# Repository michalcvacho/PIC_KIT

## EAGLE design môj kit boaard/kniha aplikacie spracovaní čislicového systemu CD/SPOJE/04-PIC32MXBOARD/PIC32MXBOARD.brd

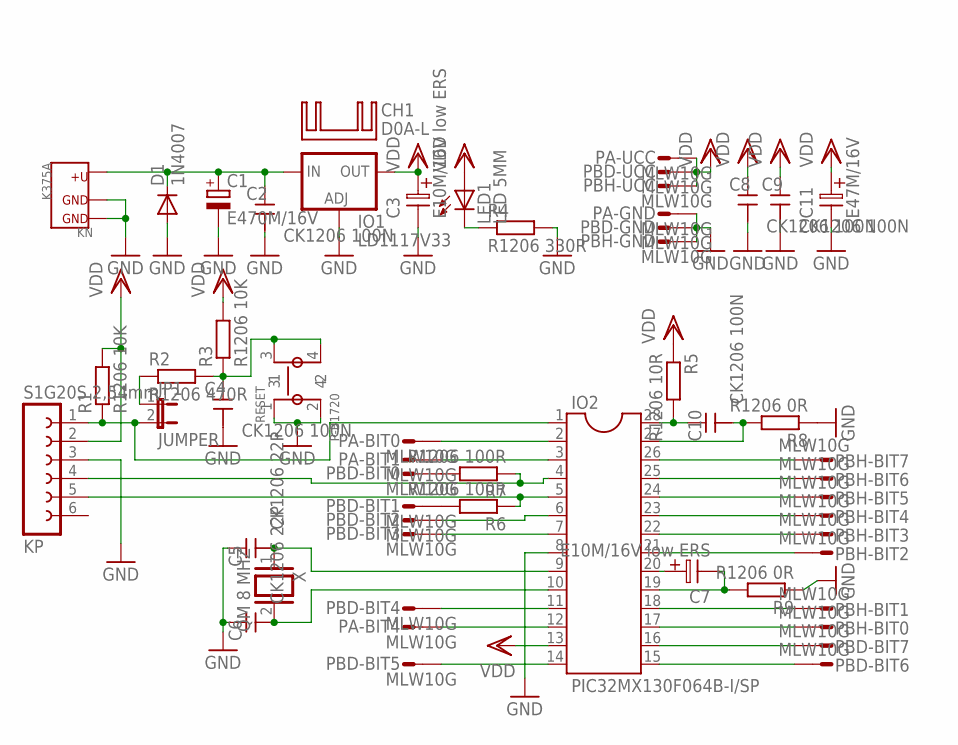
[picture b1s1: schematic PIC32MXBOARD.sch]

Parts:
C1: E470M/16V; E5-10,5
C2, C4, C8, C9, C10: CK1206 100N; CK+
C3, C7: E10M/16V low ERS; ES-2,5L
C5, C6: CK1206 22P; CK+
C11: E47M/16V; ES-2,5L
CH1: D0A-L; D02A-L
D1: 1N4007; DO41-10
IO1: LD1117V33; TO220L1
IO2: PIC32MX130F064B-I/SP; DIL28-3
JP1: JUMPER; JP1
KN: K375A
KP: S1G20S 2,54mm; FE06
LED1: LED 5MM; LED5MM
PA: MLW10G
PBD: MLW10G
PBH: MLW10G
R1, R3: R1206 10K; R1206
R2: R1206 470R; R1206
R4: R1206 330R; R1206
R5: R1206 10R; R1206
R6, R7: R1206 100R; R1206
R8, R9: R1206 0R; R1206
RESET: P-B1720
U$2: RAM
X: QM 8 MHZ; QS

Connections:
5V: C1.+, C2.1, D1.C, IO1.3 (IN), KN.2
GND: C1.-, C2.2, C3.2, C4.2, C5.1, C6.1, C8.2, C9.2, C11.2, D1.A, IO1.1 (ADJ), IO2.8, KN.1, KN.3, KP.3, PA.10, PBD.10, PBH.10, R4.2, R8.1, R9.1, RESET.1, RESET.2
unnamed: IO2.1, JP1.2, KP.1, R1.1
unnamed: C4.1, R2.2, R3.1, RESET.3, RESET.4
unnamed: IO2.4, KP.4, R7.1
unnamed: JP1.1, R2.1
unnamed: LED1.K (C), R4.1
unnamed: IO2.5, KP.5, R6.1
unnamed: C5.2, IO2.9, X.1
unnamed: C6.2, IO2.10, X.2
unnamed: IO2.2, PA.9
unnamed: IO2.3, PA.8
unnamed: C10.2, IO2.27, R8.2
unnamed: C7.2, IO2.19, R9.2
unnamed: IO2.12, PA.5
unnamed: PBD.9, R7.2
unnamed: PBD.8, R6.2
unnamed: IO2.6, PBD.7
unnamed: IO2.7, PBD.6
unnamed: IO2.11, PBD.5
unnamed: IO2.14, PBD.4
unnamed: IO2.15, PBD.3
unnamed: IO2.16, PBD.2
unnamed: IO2.17, PBH.9
unnamed: IO2.26, PBH.2
unnamed: IO2.25, PBH.3
unnamed: IO2.24, PBH.4
unnamed: IO2.23, PBH.5
unnamed: IO2.22, PBH.6
unnamed: IO2.21, PBH.7
unnamed: IO2.18, PBH.8
unnamed: C7.1, IO2.20
unnamed: C10.1, IO2.28, R5.2
VDD: C3.1, C8.1, C9.1, C11.1, IO1.2 (OUT), IO2.13, KP.2, LED1.A, PA.1, PBD.1, PBH.1, R1.2, R3.2, R5.1

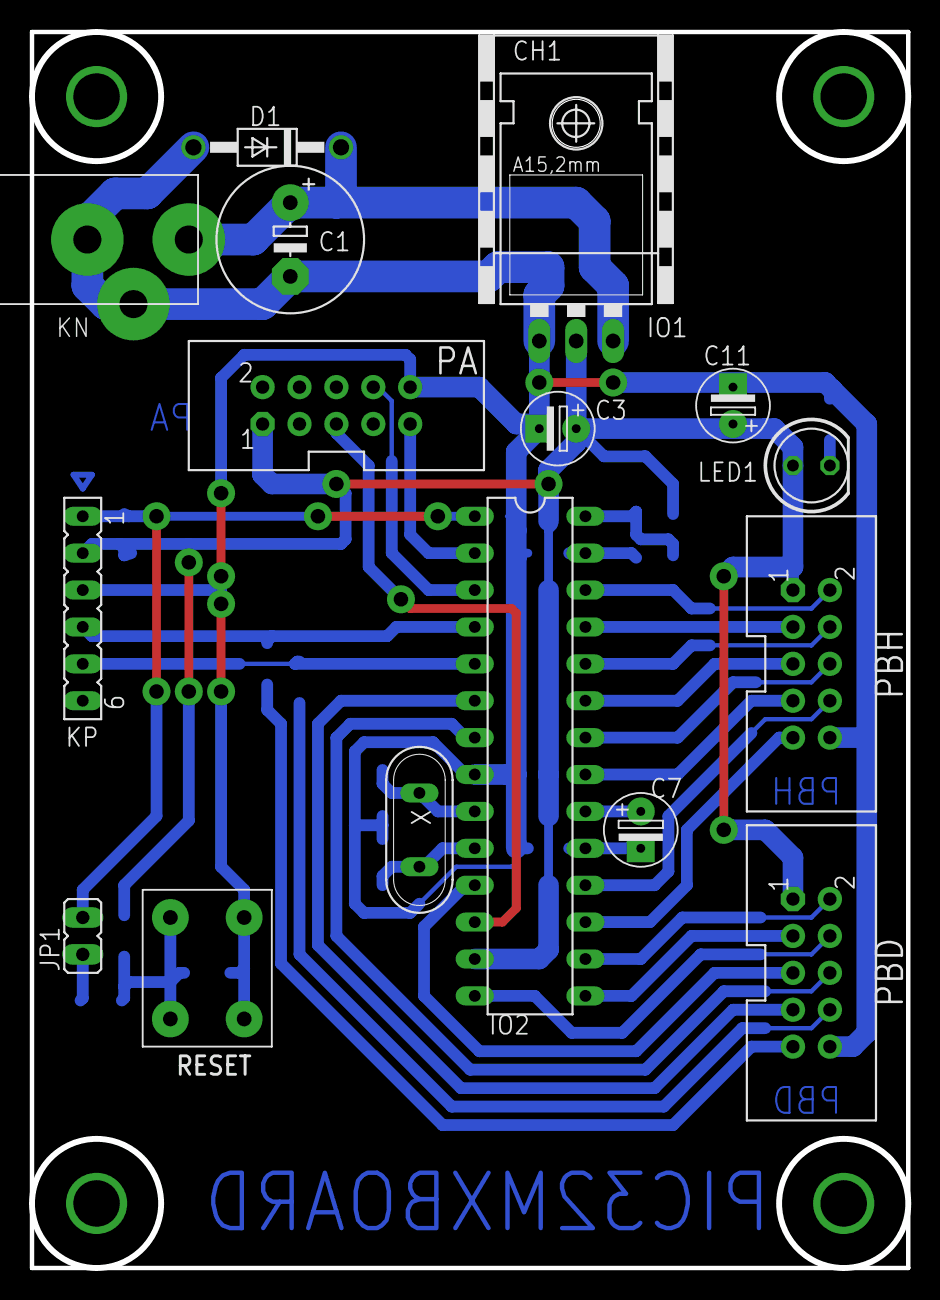
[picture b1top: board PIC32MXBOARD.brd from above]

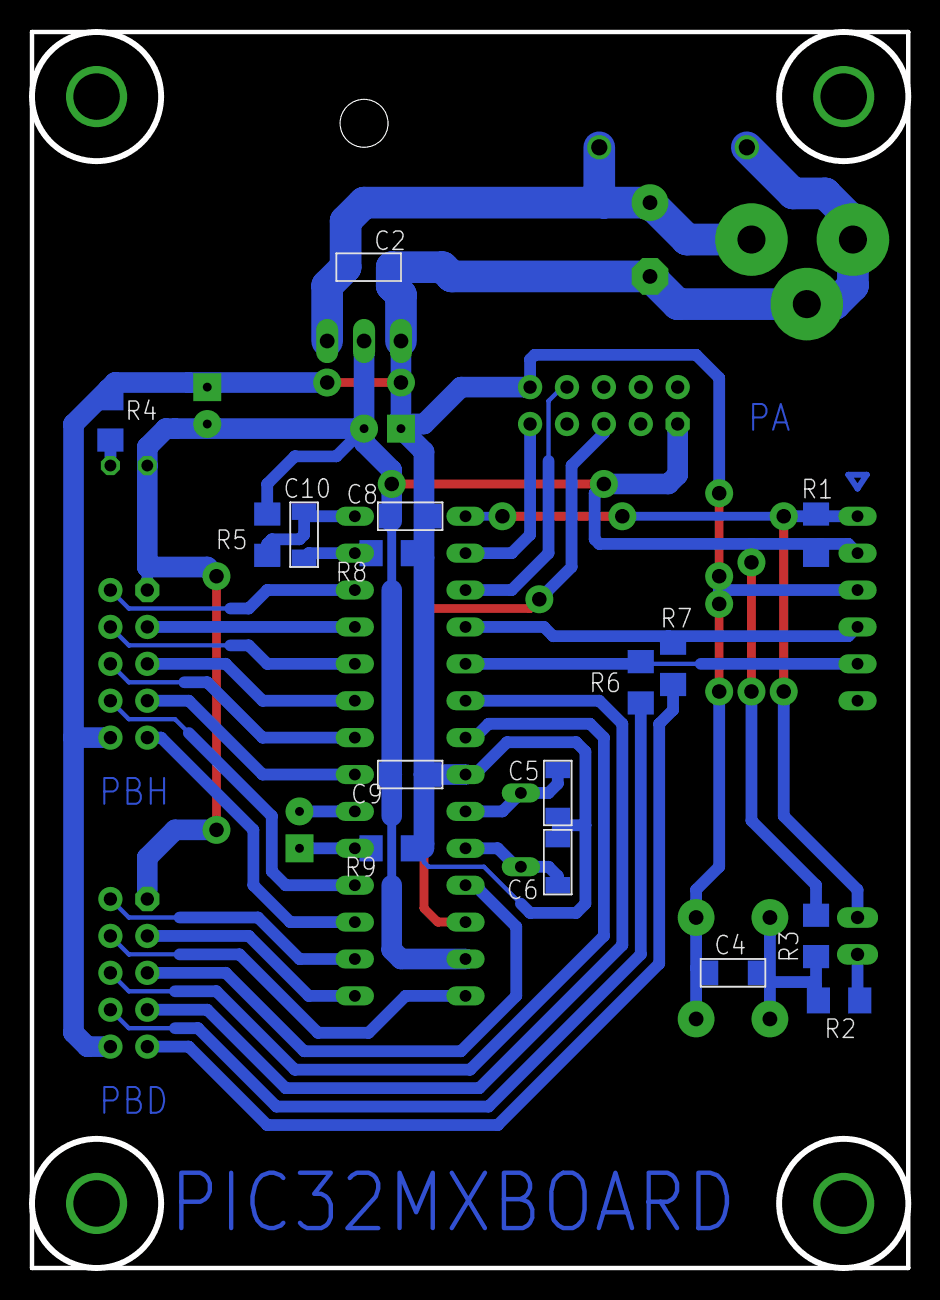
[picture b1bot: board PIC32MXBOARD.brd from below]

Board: 2 copper layers, 60.3 x 85.1 mm, 34 parts (16 on the bottom side), 34 nets.

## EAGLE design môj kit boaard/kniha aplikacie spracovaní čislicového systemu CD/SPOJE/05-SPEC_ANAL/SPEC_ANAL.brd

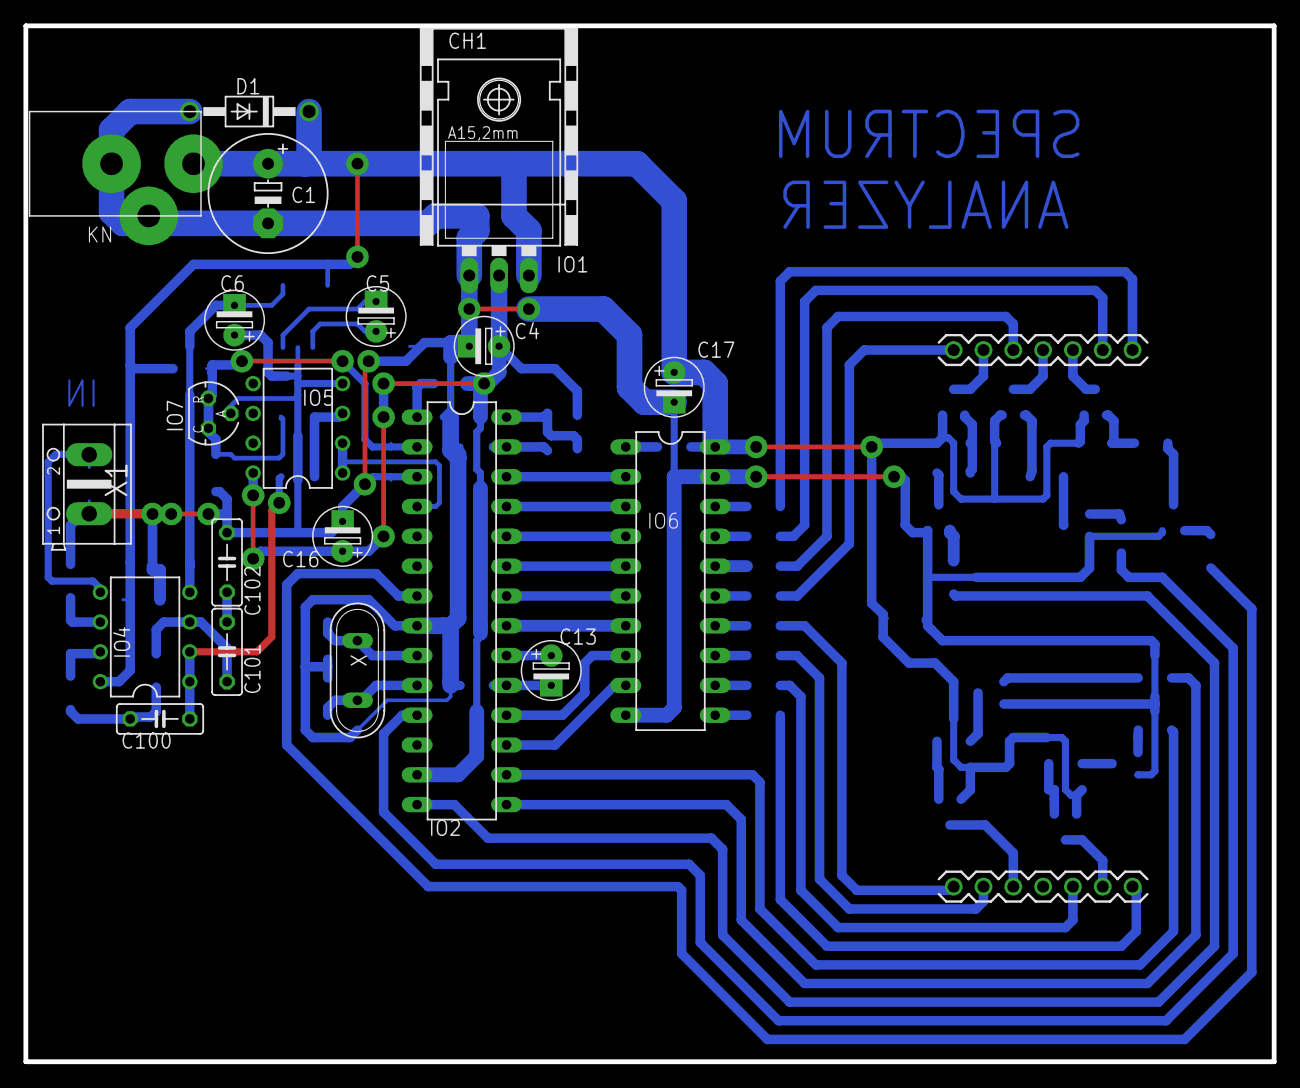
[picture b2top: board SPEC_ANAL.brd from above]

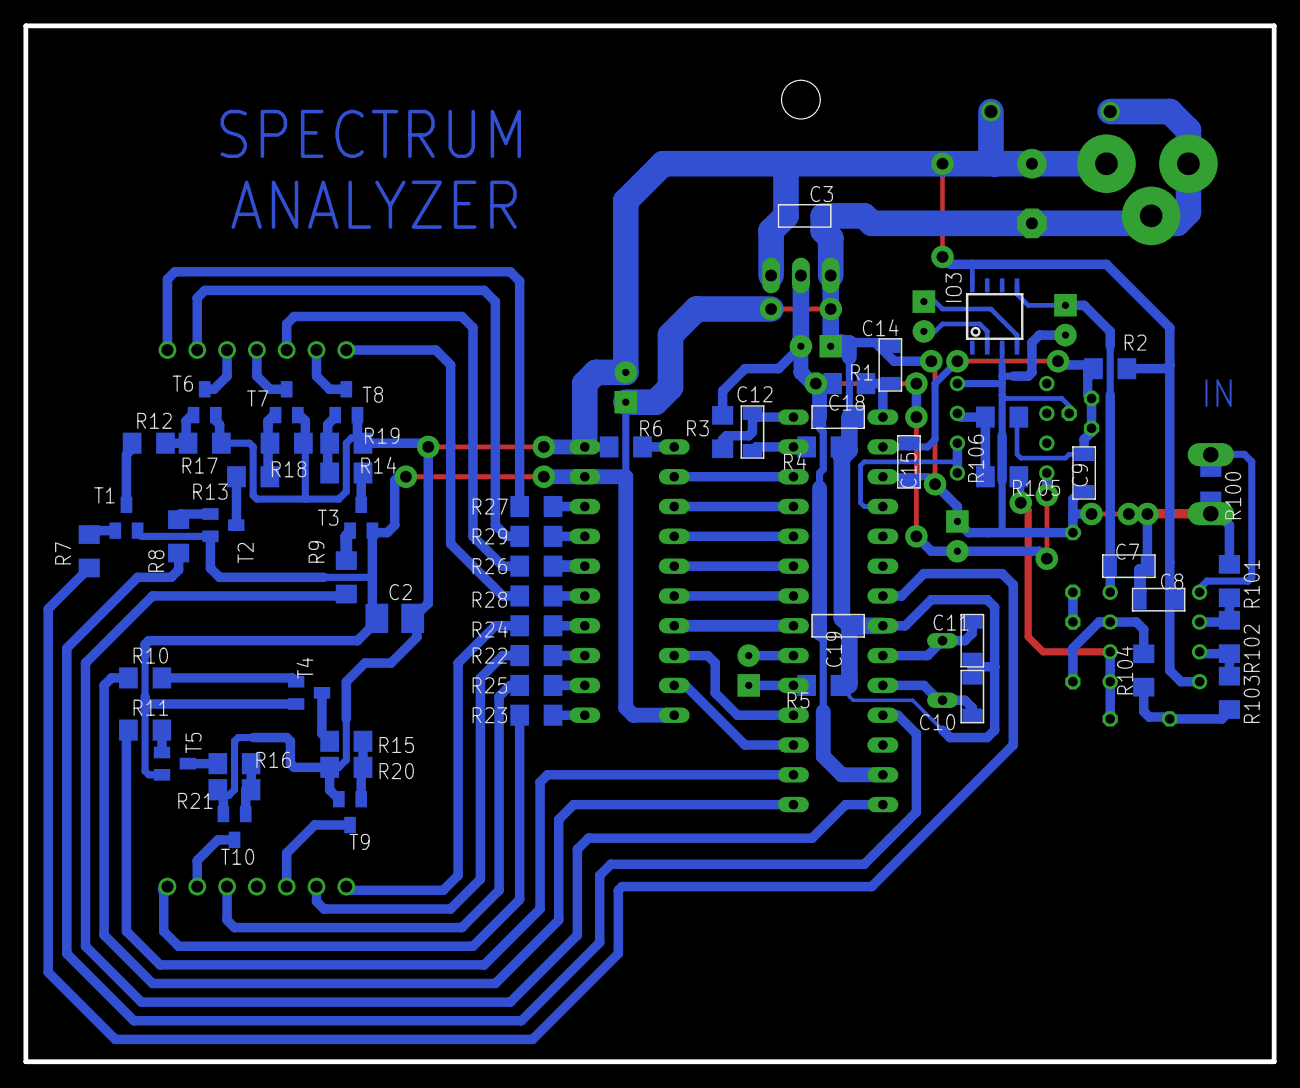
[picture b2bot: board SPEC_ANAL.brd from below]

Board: 2 copper layers, 106.4 x 88.3 mm, 81 parts (59 on the bottom side), 73 nets.

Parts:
C1: E470M/16V; E5-10,5
C2: E10M/16V; B/3528-21R
C3, C7, C8, C12, C15, C18, C19: CK1206 100N; CK+
C4, C13: E10M/16V low ERS; ES-2,5L
C5, C6: E10M/16V; ES-2,5L
C9, C14: CK1206 1N; CK+
C10, C11: CK1206 22P; CK+
C16, C17: E47M/16V; ES-2,5L
C100, C101, C102: 1N; C050-025X075
CH1: D0A-L; D02A-L
D1: 1N4007; DO41-10
DISP: MATRIX_60MM_14PIN
IO1: LD1117V33; TO220L1
IO2: PIC32MX130F064B-I/SP; DIL28-3
IO3: TL7660D; D_R-PDSO-G08
IO4: TL072P; DIL08
IO5: MCP6002P; DIL08
IO6: 74HCT245; DIL20
IO7: TL431; TO92-CLP
KN: K375A
R1, R101, R102, R105, R106: R1206 10K; R1206
R2: R1206 330R; R1206
R3: R1206 10R; R1206
R4, R5, R6: R1206 0R; R1206
R7, R8, R9, R10, R11, R12, R13, R14, R15, R16: R1206 1K; R1206
R17, R18, R19, R20, R21, R100: R1206 100K; R1206
R22, R23, R24, R25, R26, R27, R28, R29: R1206 100R; R1206
R103, R104: R1206 13K3; R1206
T1, T2, T3, T4, T5: BC848; SOT23
T6, T7, T8, T9, T10: SOT23-BEC
X: QM 8 MHZ; QS
X1: AK500/2

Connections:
+5V: C1.+, C2.+, C3.1, C8.2, C17.1, D1.C, IO1.3, IO3.8, IO4.8, IO6.20, KN.2, R2.2, R6.1, R17.1, R18.1, R19.1, R20.1, R21.1, T6.E, T7.E, T8.E, T9.E, T10.E
GND: C1.-, C2.-, C3.2, C4.2, C6.1, C7.2, C8.1, C9.2, C10.1, C11.1, C14.2, C15.2, C16.2, C17.2, C18.2, C19.2, C102.2, D1.A, IO1.1, IO2.3, IO2.8, IO3.3, IO5.4, IO6.10, IO6.19, IO7.A, KN.1, KN.3, R4.1, R5.1, R100.2, R101.2, T1.2, T2.2, T3.2, T4.2, T5.2, X1.1
unnamed: C14.1, IO2.1, R1.1
unnamed: IO2.7, R7.2
unnamed: IO2.26, IO6.2
unnamed: IO2.25, IO6.3
unnamed: R10.2, T4.1
unnamed: IO2.24, IO6.4
unnamed: C11.2, IO2.9, X.1
unnamed: C10.2, IO2.10, X.2
unnamed: IO2.23, IO6.5
unnamed: IO2.22, IO6.6
unnamed: C12.2, IO2.27, R4.2
unnamed: C13.2, IO2.19, R5.2
unnamed: IO2.21, IO6.7
unnamed: IO2.18, IO6.8
unnamed: IO2.17, IO6.9
unnamed: R15.1, T4.3
unnamed: IO2.15, R10.1
unnamed: R9.2, T3.1
unnamed: R15.2, R20.2, T9.B
unnamed: DISP.10, T6.C
unnamed: DISP.11, T7.C
unnamed: DISP.13, T8.C
unnamed: IO6.11, R23.2
unnamed: IO6.15, R28.2
unnamed: IO6.16, R26.2
unnamed: IO6.17, R29.2
unnamed: IO6.18, R27.2
unnamed: IO6.13, R22.2
unnamed: IO6.14, R24.2
unnamed: IO6.12, R25.2
unnamed: C13.1, IO2.20
unnamed: C12.1, IO2.28, R3.2
unnamed: DISP.14, R28.1
unnamed: DISP.8, R27.1
unnamed: DISP.12, R26.1
unnamed: DISP.5, R25.1
unnamed: DISP.1, R24.1
unnamed: DISP.7, R23.1
unnamed: DISP.2, R22.1
unnamed: DISP.9, R29.1
unnamed: IO2.11, R8.2
unnamed: IO2.16, R11.1
unnamed: R11.2, T5.1
unnamed: R16.1, T5.3
unnamed: R16.2, R21.2, T10.B
unnamed: DISP.6, T10.C
unnamed: DISP.3, T9.C
unnamed: R14.1, T3.3
unnamed: R14.2, R19.2, T8.B
unnamed: R7.1, T1.1
unnamed: IO2.14, R9.1
unnamed: R8.1, T2.1
unnamed: R13.1, T2.3
unnamed: R13.2, R18.2, T7.B
unnamed: IO2.4, IO5.1, IO5.2
unnamed: R12.1, T1.3
unnamed: R12.2, R17.2, T6.B
unnamed: IO5.3, R105.1, R106.1
unnamed: IO4.6, R101.1, R102.1
unnamed: IO4.5, R100.1, X1.2
unnamed: C9.1, C15.1, IO2.2, IO7.C, IO7.R, R2.1, R106.2
unnamed: C6.2, C7.1, IO3.5, IO4.4
unnamed: C5.1, IO3.2
unnamed: C5.2, IO3.4
unnamed: IO6.1, R6.2
unnamed: C100.1, R103.1, R104.2
unnamed: C101.1, IO4.3, R104.1
unnamed: C100.2, IO4.1, IO4.2, R105.2
unnamed: C101.2, C102.1
unnamed: IO4.7, R102.2, R103.2
VDD: C4.1, C16.1, C18.1, C19.1, IO1.2, IO2.13, IO5.8, R1.2, R3.1

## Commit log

2018-01-22 first commnit
2018-01-26 add blinking_led
2018-02-02 updeting
2018-02-13 13.02.2018
2018-04-16 cfds
2018-05-02 2.05
